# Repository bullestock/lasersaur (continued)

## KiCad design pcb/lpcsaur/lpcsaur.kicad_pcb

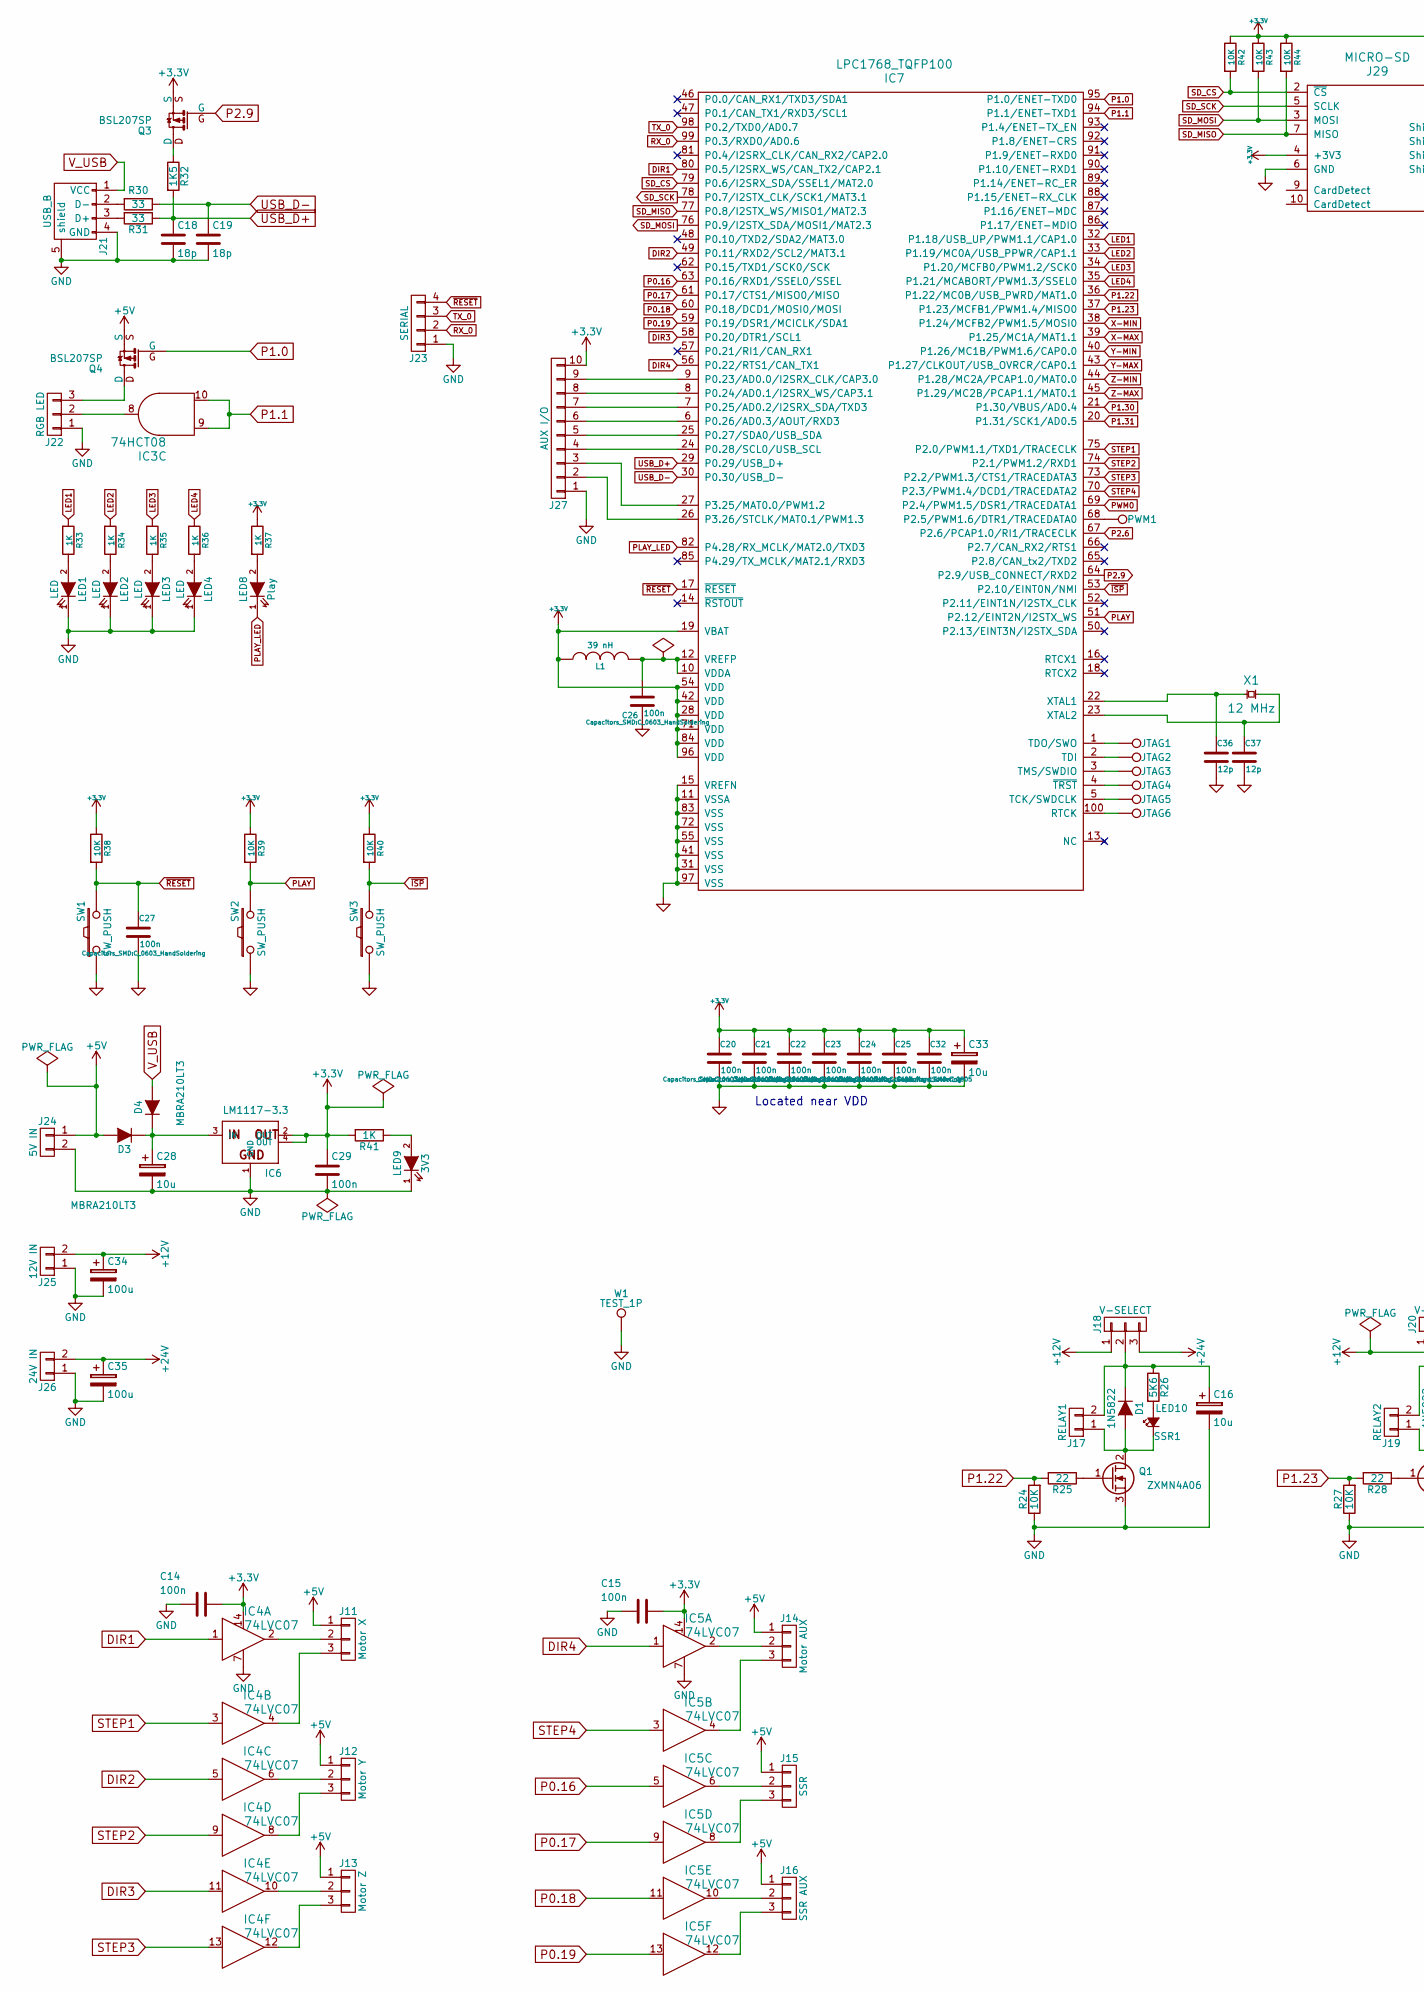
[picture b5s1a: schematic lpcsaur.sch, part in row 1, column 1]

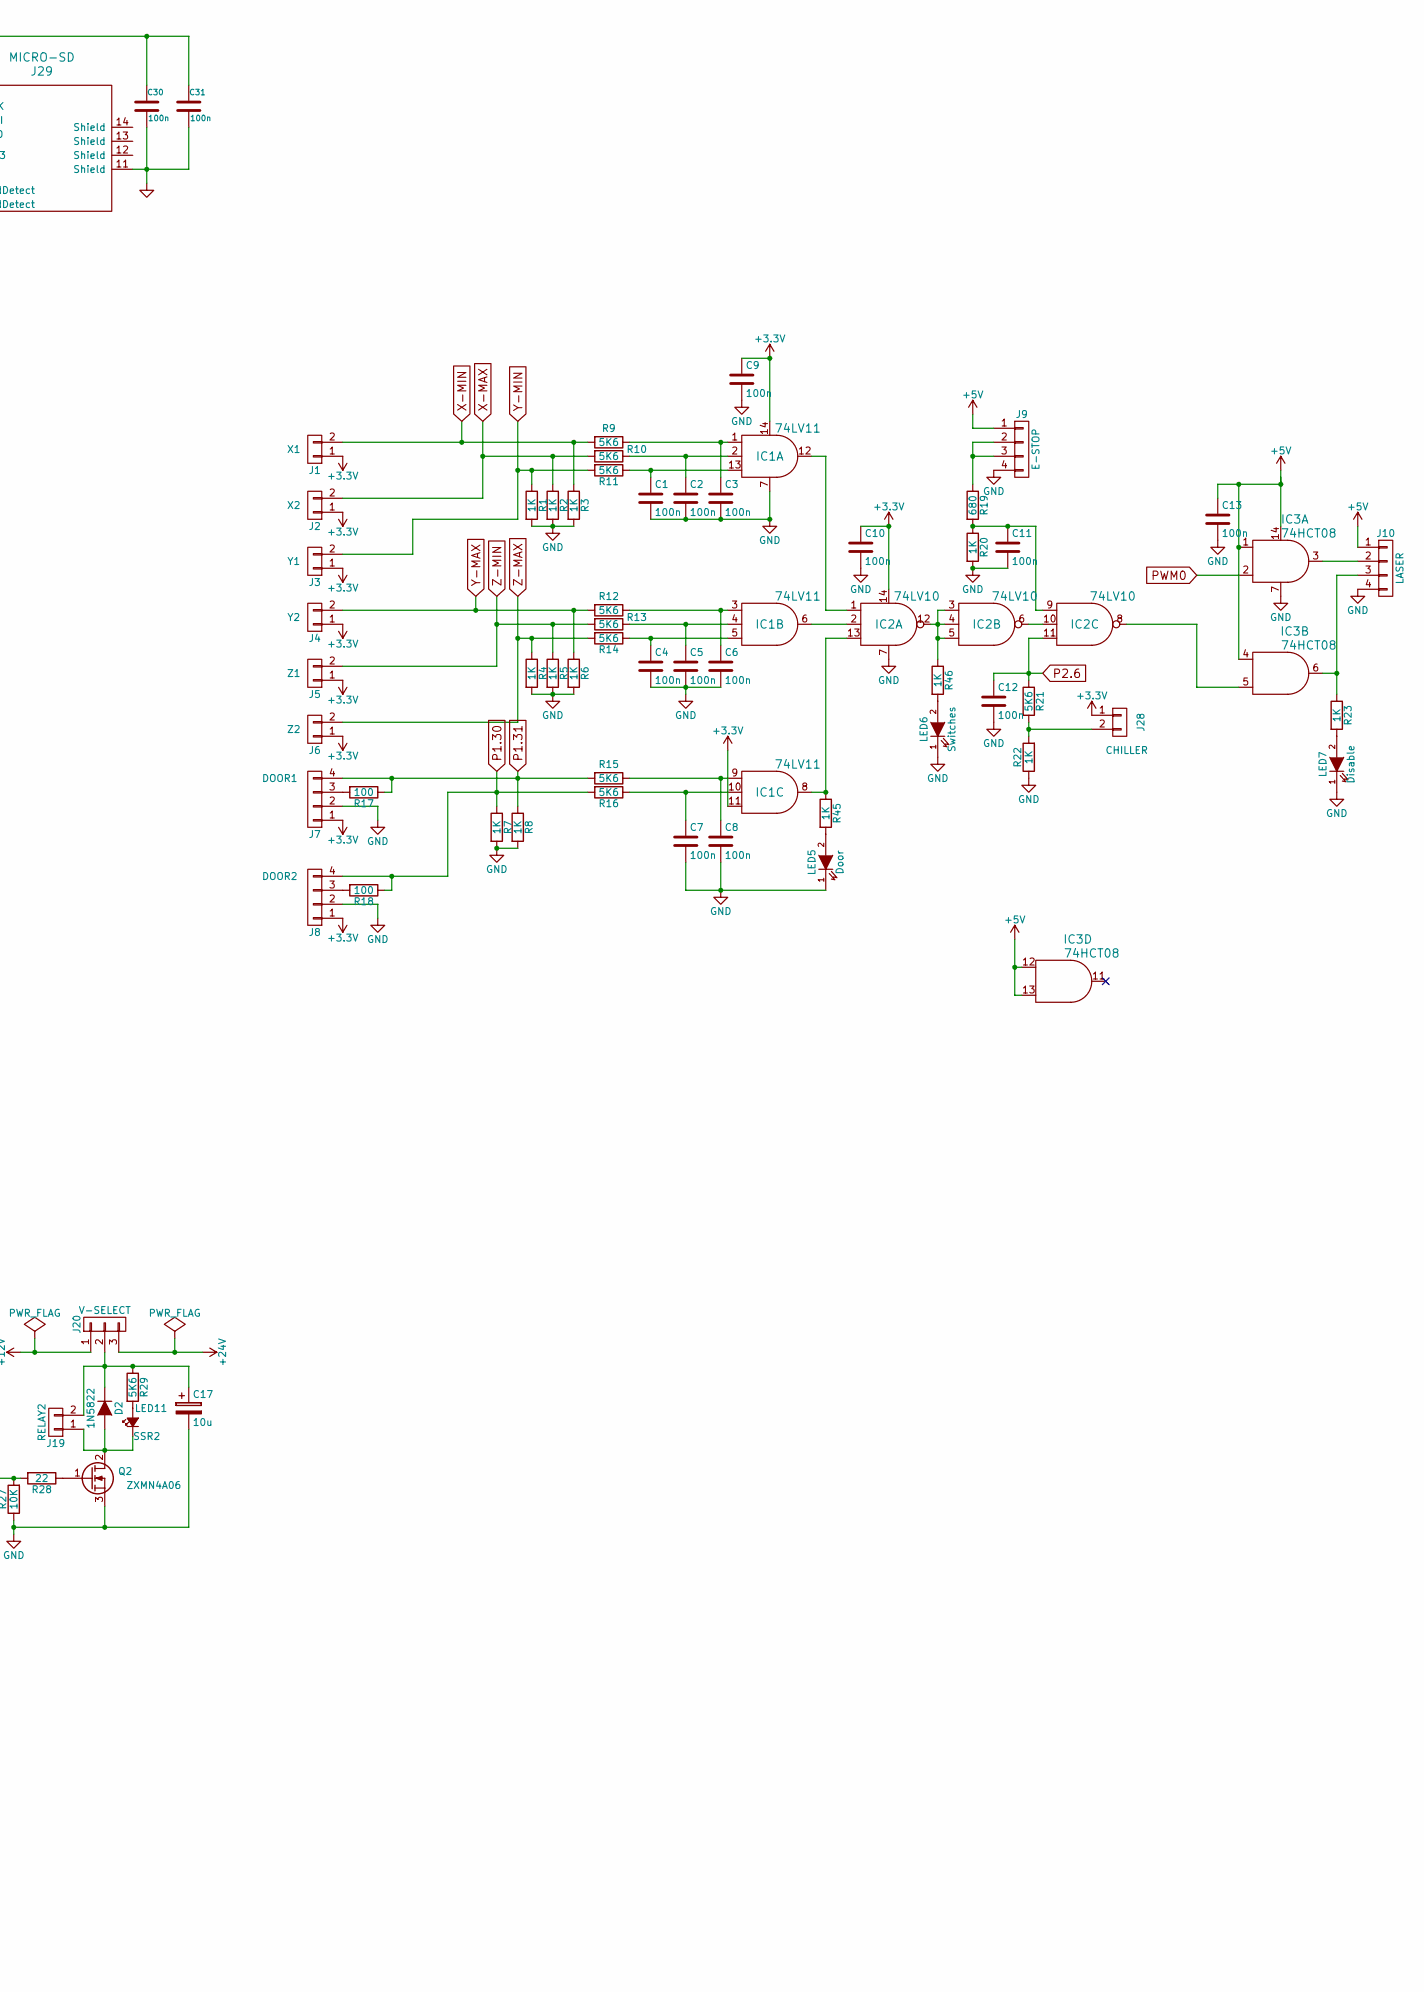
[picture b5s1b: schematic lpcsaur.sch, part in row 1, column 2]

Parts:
C1, C2, C3, C4, C5, C6, C7, C8, C9, C10, C11, C12, C13, C14, C15, C29, C30, C31, C32: 100n; C_0805
C16, C17, C28, C33: 10u; TantalC_SizeD_EIA-7343_Reflow
C18, C19: 18p; C_0603
C20, C21, C22, C23, C24, C25, C26, C27: 100n; C_0603_HandSoldering
C34, C35: 100u; c_elec_6.3x7.7
C36, C37: 12p; C_0603
D1, D2: 1N5822; Diode_DO-41_SOD81_Vertical_KathodeUp
D3, D4: MBRA210LT3; SMA_Standard
IC1: 74LV11; SOIC-14_N
IC2: 74LV10; SSOP-14
IC3: 74HCT08; SOIC-14_N
IC4, IC5: 74LVC07; SOIC-14_N
IC6: LM1117-3.3; SOT-223
IC7: LPC1768_TQFP100; TQFP-100_14x14mm_Pitch0.5mm
J1: X1; JST_PH_B2B-PH-K_02x2.00mm_Straight
J2: X2; JST_PH_B2B-PH-K_02x2.00mm_Straight
J3: Y1; JST_PH_B2B-PH-K_02x2.00mm_Straight
J4: Y2; JST_PH_B2B-PH-K_02x2.00mm_Straight
J5: Z1; JST_PH_B2B-PH-K_02x2.00mm_Straight
J6: Z2; JST_PH_B2B-PH-K_02x2.00mm_Straight
J7: DOOR1; JST_PH_B4B-PH-K_04x2.00mm_Straight
J8: DOOR2; JST_PH_B4B-PH-K_04x2.00mm_Straight
J9: E-STOP; JST_PH_B4B-PH-K_04x2.00mm_Straight
J10: LASER; JST_PH_B4B-PH-K_04x2.00mm_Straight
J11: Motor X; JST_PH_B3B-PH-K_03x2.00mm_Straight
J12: Motor Y; JST_PH_B3B-PH-K_03x2.00mm_Straight
J13: Motor Z; JST_PH_B3B-PH-K_03x2.00mm_Straight
J14: Motor AUX; JST_PH_B3B-PH-K_03x2.00mm_Straight
J15: SSR; JST_PH_B3B-PH-K_03x2.00mm_Straight
J16: SSR AUX; JST_PH_B3B-PH-K_03x2.00mm_Straight
J17: RELAY1; JST_PH_B2B-PH-K_02x2.00mm_Straight
J18, J20: V-SELECT; Socket_Strip_Straight_1x03
J19: RELAY2; JST_PH_B2B-PH-K_02x2.00mm_Straight
J21: USB_B
J22: RGB LED; JST_PH_B3B-PH-K_03x2.00mm_Straight
J23: SERIAL; JST_PH_B4B-PH-K_04x2.00mm_Straight
J24: 5V IN; TerminalBlock_WAGO-804_RM5mm_2pol
J25: 12V IN; TerminalBlock_WAGO-804_RM5mm_2pol
J26: 24V IN; TerminalBlock_WAGO-804_RM5mm_2pol
J27: AUX I/O; JST_PH_B10B-PH-K_10x2.00mm_Straight
J28: CHILLER; JST_PH_B2B-PH-K_02x2.00mm_Straight
J29: MICRO-SD; Conn_uSDcard
JTAG1, JTAG2, JTAG3, JTAG4, JTAG5, JTAG6: TEST_1P; TP_Oblong
L1: 39 nH; R_0603
LED1, LED2, LED3, LED4: LED; LED_0603
LED5: Door; LED_0603
LED6: Switches; LED_0603
LED7: Disable; LED_0603
LED8: Play; LED_0603
LED9: 3V3; LED_0603
LED10: SSR1; LED_0603
LED11: SSR2; LED_0603
PWM1: TEST_1P; TP_Oblong
Q1, Q2: ZXMN4A06; SOT-223-3
Q3, Q4: BSL207SP; SSOP-6-3
R1, R2, R3, R4, R5, R6, R7, R8, R20, R22, R23, R33, R34, R35, R36, R37, R41, R45, R46: 1K; R_0603
R9, R10, R11, R12, R13, R14, R15, R16, R21, R26, R29: 5K6; R_0603
R17, R18: 100; R_0603
R19: 680; R_0603
R24, R27, R38, R39, R40, R42, R43, R44: 10K; R_0603
R25, R28: 22; R_0603
R30, R31: 33; R_0603
R32: 1K5; R_0603
SW1, SW3: SW_PUSH; TactileSwitch
SW2: SW_PUSH; TactileSwitchUpright
W1: TEST_1P; TP_0805
X1: 12 MHz; CrystalSmd2.5x3.2

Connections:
+3V3: C9.1, C10.1, C14.1, C15.1, C20.1, C21.1, C22.1, C23.1, C24.1, C25.1, C29.1, C30.1, C31.1, C32.1, C33.1, IC1.11 (3C), IC1.14 (VDD), IC2.14 (VDD), IC4.14 (VDD), IC5.14 (VDD), IC6.2 (OUT), IC6.4 (OUT), IC7.19 (VBAT), IC7.28 (VDD), IC7.42 (VDD), IC7.54 (VDD), IC7.71 (VDD), IC7.84 (VDD), IC7.96 (VDD), J1.1, J2.1, J3.1, J4.1, J5.1, J6.1, J7.1, J8.1, J27.10, J28.1, J29.4 (+3V3), L1.1, Q3.S, R37.1, R38.1, R39.1, R40.1, R41.2, R42.1, R43.1, R44.1
+5V: C13.1, D3.2 (A), IC3.1 (1A), IC3.4 (2A), IC3.12 (4A), IC3.13 (4B), IC3.14 (VDD), J9.1, J10.1, J11.1, J12.1, J13.1, J14.1, J15.1, J16.1, J24.1, Q4.S
+12V: C34.1, J18.1, J20.1, J25.2
+24V: C35.1, J18.3, J20.3, J26.2
DIR1: IC4.1 (1A), IC7.80 (P0.5/I2SRX_WS/CAN_TX2/CAP2.1)
DIR2: IC4.5 (3A), IC7.49 (P0.11/RXD2/SCL2/MAT3.1)
DIR3: IC4.11 (5A), IC7.58 (P0.20/DTR1/SCL1)
DIR4: IC5.1 (1A), IC7.56 (P0.22/RTS1/CAN_TX1)
GND: C1.2, C2.2, C3.2, C4.2, C5.2, C6.2, C7.2, C8.2, C9.2, C10.2, C11.2, C12.2, C13.2, C14.2, C15.2, C16.2, C17.2, C18.2, C19.2, C20.2, C21.2, C22.2, C23.2, C24.2, C25.2, C26.2, C27.2, C28.2, C29.2, C30.2, C31.2, C32.2, C33.2, C34.2, C35.2, C36.2, C37.2, IC1.7 (VSS), IC2.7 (VSS), IC3.7 (VSS), IC4.7 (VSS), IC5.7 (VSS), IC6.1 (GND), IC7.11 (VSSA), IC7.15 (VREFN), IC7.31 (VSS), IC7.41 (VSS), IC7.55 (VSS), IC7.72 (VSS), IC7.83 (VSS), IC7.97 (VSS), J7.2, J8.2, J9.4, J10.4, J21.4 (GND), J21.5 (shield), J22.1, J23.1, J24.2, J25.1, J26.1, J27.1, J29.6 (GND), J29.9 (CardDetect), J29.11 (Shield), LED1.1 (K), LED2.1 (K), LED3.1 (K), LED4.1 (K), LED5.1 (K), LED6.1 (K), LED7.1 (K), LED9.1 (K), Q1.3 (S), Q2.3 (S), R1.2, R2.2, R3.2, R4.2, R5.2, R6.2, R7.2, R8.2, R20.2, R22.1, R24.1, R27.1, SW1.1, SW2.1, SW3.1, W1.1
LED1: IC7.32 (P1.18/USB_UP/PWM1.1/CAP1.0), R33.2
LED2: IC7.33 (P1.19/MC0A/USB_PPWR/CAP1.1), R34.2
LED3: IC7.34 (P1.20/MCFB0/PWM1.2/SCK0), R35.2
LED4: IC7.35 (P1.21/MCABORT/PWM1.3/SSEL0), R36.2
unnamed: C1.1, IC1.13 (1C), R11.1
unnamed: C2.1, IC1.2 (1B), R10.1
unnamed: C3.1, IC1.1 (1A), R9.1
unnamed: C4.1, IC1.5 (2C), R14.1
unnamed: C5.1, IC1.4 (2B), R13.1
unnamed: C6.1, IC1.3 (2A), R12.1
unnamed: C7.1, IC1.10 (3B), R16.1
unnamed: C8.1, IC1.9 (3A), R15.1
unnamed: C11.1, IC2.9 (3A), R19.2, R20.1
unnamed: C16.1, D1.1 (K), J17.2, J18.2, R26.1
unnamed: C17.1, D2.1 (K), J19.2, J20.2, R29.1
unnamed: C26.1, IC7.10 (VDDA), IC7.12 (VREFP), L1.2
unnamed: C28.1, D3.1 (K), D4.1 (K), IC6.3 (IN)
unnamed: C36.1, IC7.22 (XTAL1), X1.1
unnamed: C37.1, IC7.23 (XTAL2), X1.2
unnamed: D1.2 (A), J17.1, LED10.1 (K), Q1.2 (D)
unnamed: D2.2 (A), J19.1, LED11.1 (K), Q2.2 (D)
unnamed: IC1.6 (2Y), IC2.2 (1B)
unnamed: IC1.8 (3Y), IC2.13 (1C), R45.1
unnamed: IC1.12 (1Y), IC2.1 (1A)
unnamed: IC2.8 (3Y), IC3.5 (2B)
unnamed: IC2.6 (2Y), IC2.10 (3B)
unnamed: IC2.3 (2A), IC2.4 (2B), IC2.5 (2C), IC2.12 (1Y), R46.1
unnamed: IC3.3 (1Y), J10.2
unnamed: IC3.6 (2Y), J10.3, R23.1
unnamed: IC3.8 (3Y), J22.2
unnamed: IC4.2 (1Y), J11.2
unnamed: IC4.4 (1Y), J11.3
unnamed: IC4.6 (1Y), J12.2
unnamed: IC4.8 (1Y), J12.3
unnamed: IC4.10 (1Y), J13.2
unnamed: IC4.12 (1Y), J13.3
unnamed: IC5.2 (1Y), J14.2
unnamed: IC5.4 (1Y), J14.3
unnamed: IC5.6 (1Y), J15.2
unnamed: IC5.8 (1Y), J15.3
unnamed: IC5.10 (1Y), J16.2
unnamed: IC5.12 (1Y), J16.3
unnamed: IC7.1 (TDO/SWO), JTAG1.1
unnamed: IC7.2 (TDI), JTAG2.1
unnamed: IC7.3 (TMS/SWDIO), JTAG3.1
unnamed: IC7.4 (~TRST), JTAG4.1
unnamed: IC7.5 (TCK/SWDCLK), JTAG5.1
unnamed: IC7.6 (P0.26/AD0.3/AOUT/RXD3), J27.6
unnamed: IC7.7 (P0.25/AD0.2/I2SRX_SDA/TXD3), J27.7
unnamed: IC7.8 (P0.24/AD0.1/I2SRX_WS/CAP3.1), J27.8
unnamed: IC7.9 (P0.23/AD0.0/I2SRX_CLK/CAP3.0), J27.9
unnamed: IC7.24 (P0.28/SCL0/USB_SCL), J27.4
unnamed: IC7.25 (P0.27/SDA0/USB_SDA), J27.5
unnamed: IC7.26 (P3.26/STCLK/MAT0.1/PWM1.3), J27.2
unnamed: IC7.27 (P3.25/MAT0.0/PWM1.2), J27.3
unnamed: IC7.68 (P2.5/PWM1.6/DTR1/TRACEDATA0), PWM1.1
unnamed: IC7.100 (RTCK), JTAG6.1
unnamed: J7.3, R17.2
unnamed: J8.3, R18.2
unnamed: J9.2, J9.3, R19.1
unnamed: J21.2 (D-), R30.2
unnamed: J21.3 (D+), R31.2
unnamed: J22.3, Q4.D
unnamed: J28.2, R21.2, R22.2
unnamed: LED1.2 (A), R33.1
unnamed: LED2.2 (A), R34.1
unnamed: LED3.2 (A), R35.1
unnamed: LED4.2 (A), R36.1
unnamed: LED5.2 (A), R45.2
unnamed: LED6.2 (A), R46.2
unnamed: LED7.2 (A), R23.2
unnamed: LED8.2 (A), R37.2
unnamed: LED9.2 (A), R41.1
unnamed: LED10.2 (A), R26.2
unnamed: LED11.2 (A), R29.2
unnamed: Q1.1 (G), R25.1
unnamed: Q2.1 (G), R28.1
unnamed: Q3.D, R32.1
P0.16: IC5.5 (3A), IC7.63 (P0.16/RXD1/SSEL0/SSEL)
P0.17: IC5.9 (4A), IC7.61 (P0.17/CTS1/MISO0/MISO)
P0.18: IC5.11 (5A), IC7.60 (P0.18/DCD1/MOSI0/MOSI)
P0.19: IC5.13 (6A), IC7.59 (P0.19/DSR1/MCICLK/SDA1)
P1.0: IC7.95 (P1.0/ENET-TXD0), Q4.G
P1.1: IC3.9 (3A), IC3.10 (3B), IC7.94 (P1.1/ENET-TXD1)
P1.22: IC7.36 (P1.22/MC0B/USB_PWRD/MAT1.0), R24.2, R25.2
P1.23: IC7.37 (P1.23/MCFB1/PWM1.4/MISO0), R27.2, R28.2
P1.30: IC7.21 (P1.30/VBUS/AD0.4), J8.4, R7.1, R16.2, R18.1
P1.31: IC7.20 (P1.31/SCK1/AD0.5), J7.4, R8.1, R15.2, R17.1
P2.6: C12.1, IC2.11 (3C), IC7.67 (P2.6/PCAP1.0/RI1/TRACECLK), R21.1
P2.9: IC7.64 (P2.9/USB_CONNECT/RXD2), Q3.G
PLAY: IC7.51 (P2.12/EINT2N/I2STX_WS), R39.2, SW2.2
PLAY_LED: IC7.82 (P4.28/RX_MCLK/MAT2.0/TXD3), LED8.1 (K)
PWM0: IC3.2 (1B), IC7.69 (P2.4/PWM1.5/DSR1/TRACEDATA1)
RX_0: IC7.99 (P0.3/RXD0/AD0.6), J23.2
SD_CS: IC7.79 (P0.6/I2SRX_SDA/SSEL1/MAT2.0), J29.2 (~CS), R42.2
SD_MISO: IC7.77 (P0.8/I2STX_WS/MISO1/MAT2.3), J29.7 (MISO), R44.2
SD_MOSI: IC7.76 (P0.9/I2STX_SDA/MOSI1/MAT2.3), J29.3 (MOSI), R43.2
SD_SCK: IC7.78 (P0.7/I2STX_CLK/SCK1/MAT3.1), J29.5 (SCLK)
STEP1: IC4.3 (2A), IC7.75 (P2.0/PWM1.1/TXD1/TRACECLK)
STEP2: IC4.9 (4A), IC7.74 (P2.1/PWM1.2/RXD1)
STEP3: IC4.13 (6A), IC7.73 (P2.2/PWM1.3/CTS1/TRACEDATA3)
STEP4: IC5.3 (2A), IC7.70 (P2.3/PWM1.4/DCD1/TRACEDATA2)
TX_0: IC7.98 (P0.2/TXD0/AD0.7), J23.3
USB_D+: C18.1, IC7.29 (P0.29/USB_D+), R31.1, R32.2
USB_D-: C19.1, IC7.30 (P0.30/USB_D-), R30.1
V_USB: D4.2 (A), J21.1 (VCC)
X-MAX: IC7.39 (P1.25/MC1A/MAT1.1), J2.2, R2.1, R10.2
X-MIN: IC7.38 (P1.24/MCFB2/PWM1.5/MOSI0), J1.2, R3.1, R9.2
Y-MAX: IC7.43 (P1.27/CLKOUT/USB_OVRCR/CAP0.1), J4.2, R6.1, R12.2
Y-MIN: IC7.40 (P1.26/MC1B/PWM1.6/CAP0.0), J3.2, R1.1, R11.2
Z-MAX: IC7.45 (P1.29/MC2B/PCAP1.1/MAT0.1), J6.2, R4.1, R14.2
Z-MIN: IC7.44 (P1.28/MC2A/PCAP1.0/MAT0.0), J5.2, R5.1, R13.2
~ISP: IC7.53 (P2.10/EINT0N/NMI), R40.2, SW3.2
~RESET: C27.1, IC7.17 (~RESET), J23.4, R38.2, SW1.2

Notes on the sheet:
Located near VDD

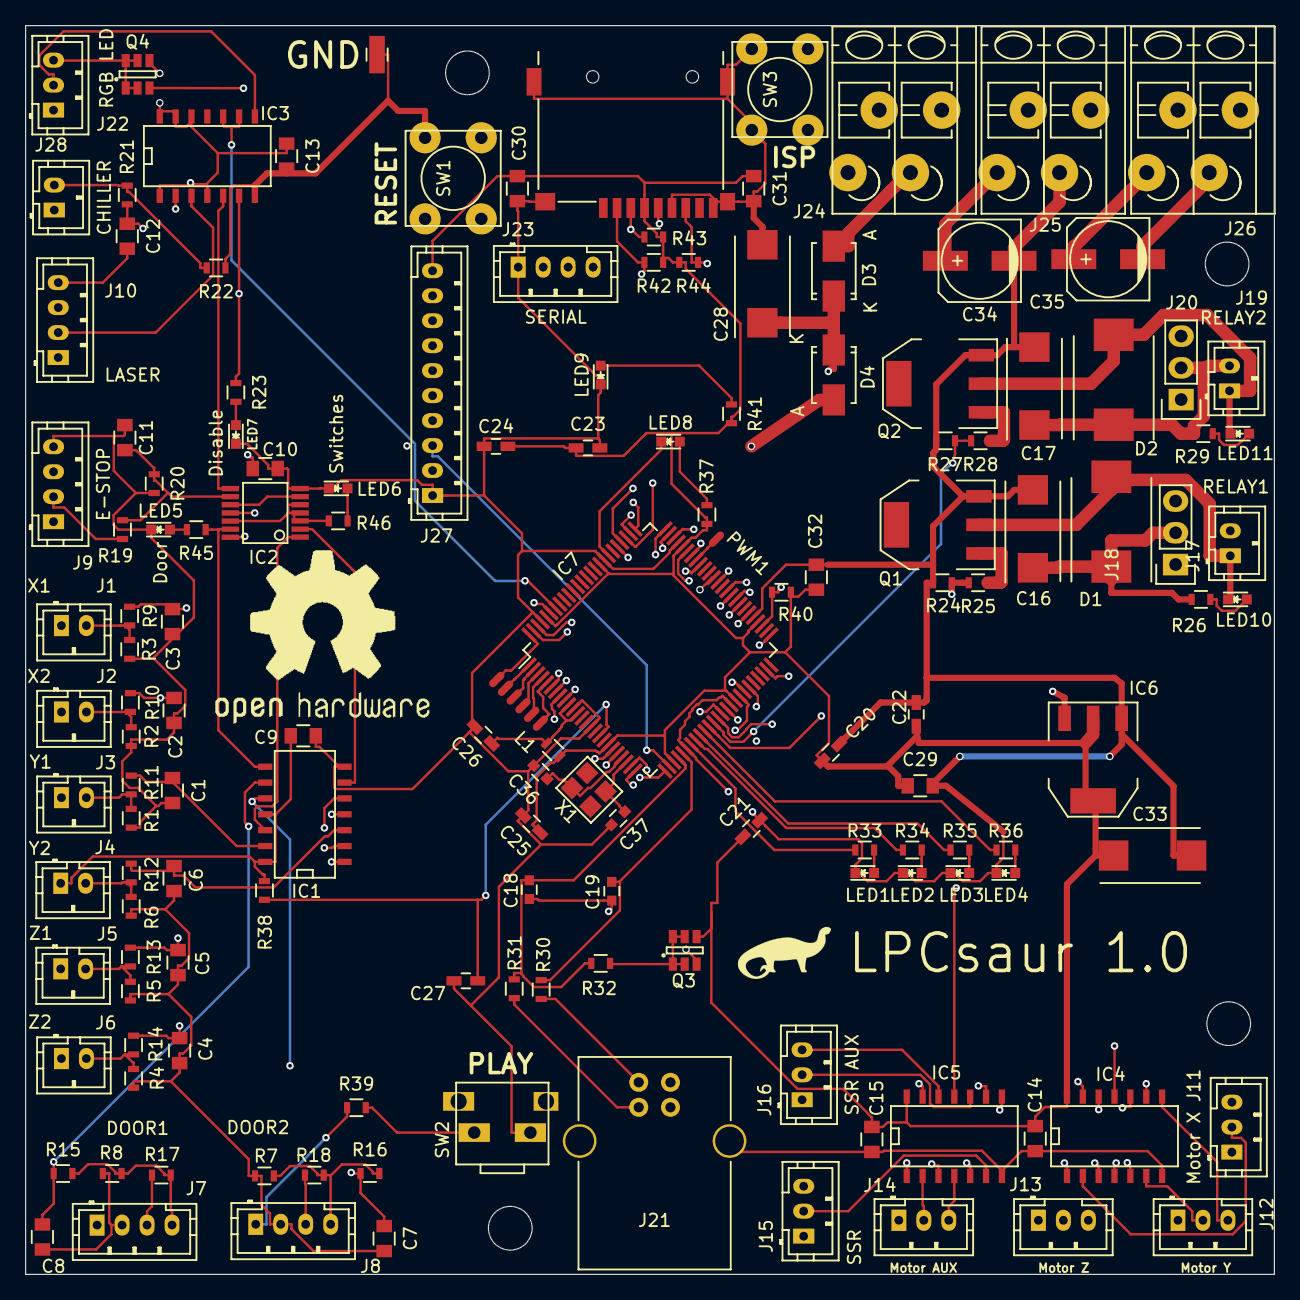
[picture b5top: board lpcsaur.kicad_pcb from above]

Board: 4 copper layers, 100.0 x 100.0 mm, 157 parts (0 on the bottom side), 123 nets.

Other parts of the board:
G1: LOGO; dino
G2: LOGO; OSHWLOGO0.75IN
HOLE1, HOLE2, HOLE3, HOLE4: MountingHole_3.5mm

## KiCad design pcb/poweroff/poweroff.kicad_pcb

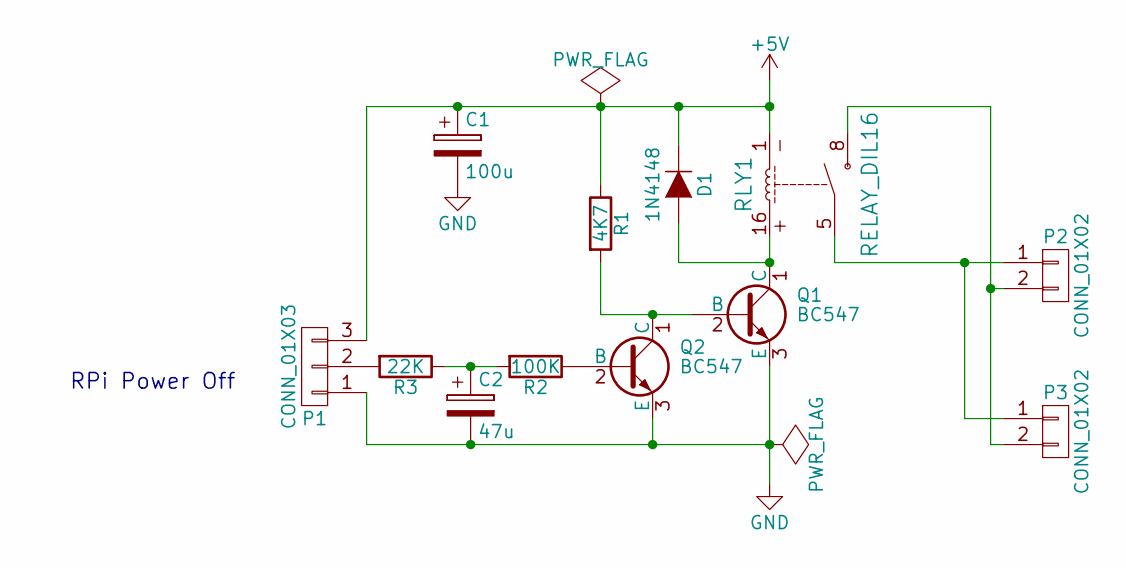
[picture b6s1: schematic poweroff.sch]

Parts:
C1: 100u; C_Disc_D6_P5
C2: 47u; C_Disc_D6_P5
D1: 1N4148; Diode_DO-41_SOD81_Horizontal_RM10
P1: CONN_01X03; JST_PH_B3B-PH-K_03x2.00mm_Straight
P2, P3: CONN_01X02; TerminalBlock_WAGO-804_RM5mm_2pol
Q1, Q2: BC547; TO-92_Molded_Narrow_CBE
R1: 4K7; Resistor_Horizontal_RM10mm
R2: 100K; Resistor_Horizontal_RM10mm
R3: 22K; Resistor_Horizontal_RM10mm
RLY1: RELAY_DIL16; DIP-16_Relay

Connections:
+5V: C1.1, D1.1 (K), P1.3, R1.1, RLY1.1
GND: C1.2, C2.2, P1.1, Q1.3 (E), Q2.3 (E)
unnamed: C2.1, R2.2, R3.1
unnamed: D1.2 (A), Q1.1 (C), RLY1.16
unnamed: P1.2, R3.2
unnamed: P2.1, P3.1, RLY1.5
unnamed: P2.2, P3.2, RLY1.8
unnamed: Q1.2 (B), Q2.1 (C), R1.2
unnamed: Q2.2 (B), R2.1

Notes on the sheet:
RPi Power Off

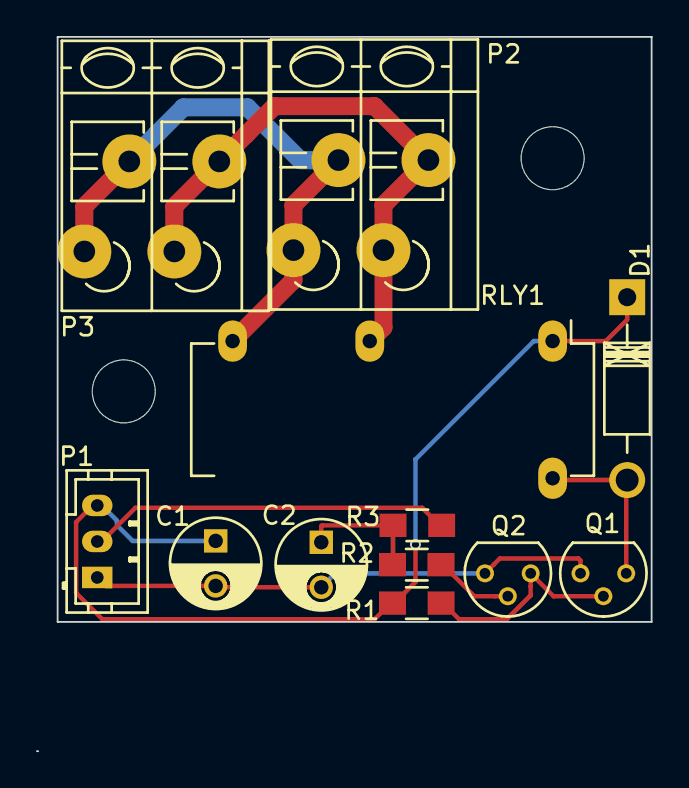
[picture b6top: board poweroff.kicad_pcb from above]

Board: 2 copper layers, 33.0 x 32.5 mm, 14 parts (0 on the bottom side), 9 nets.

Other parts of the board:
H1, H2: MountingHole_3.5mm

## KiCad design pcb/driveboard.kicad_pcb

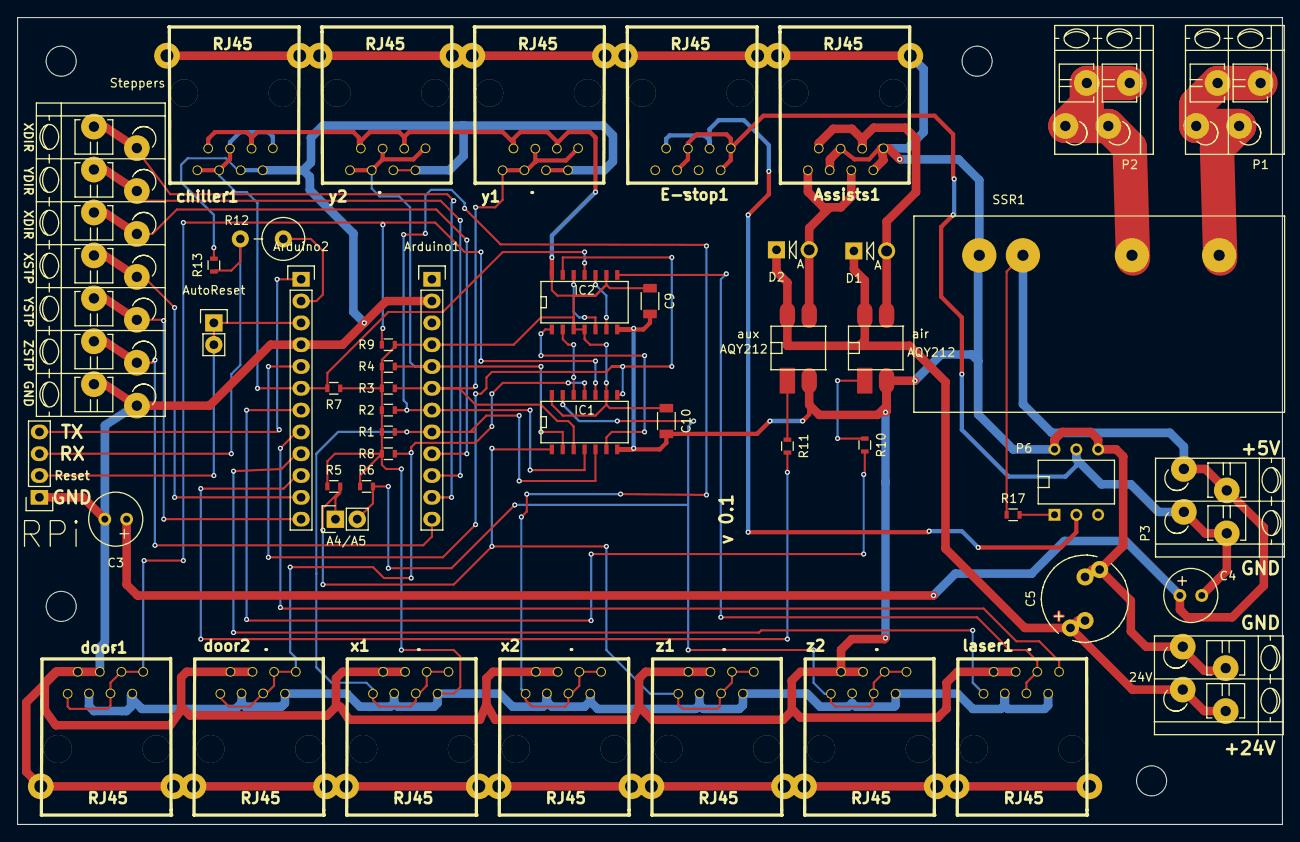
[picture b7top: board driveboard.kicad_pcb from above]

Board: 2 copper layers, 147.3 x 94.0 mm, 50 parts (0 on the bottom side), 42 nets.

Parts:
24V: CONN_01X02; TerminalBlock_WAGO-804_RM5mm_2pol
A4/A5: Header; Pin_Header_Straight_1x02
Arduino1, Arduino2: Header; Pin_Header_Straight_1x12
Assists1: RJ45; RJ45-8-shield
AutoReset: CONN_01X02; Pin_Header_Straight_1x02
C3: 10u; Elko_vert_11.2x6.3mm_RM2.5
C4: 47u; Elko_vert_11.2x6.3mm_RM2.5
C5: 1000u; Elko_vert_20x10mm_RM5to7.5
C9, C10: 100n; C_1206
D1, D2: 1N4004; Diode_DO-41_SOD81_Vertical_AnodeUp
E-stop1: RJ45; RJ45-8-shield
IC1: 7411; SOIC-14_N
IC2: 7410; SOIC-14_N
MH: MountingHole_3-5mm
P1: AC IN; TerminalBlock_WAGO-804_RM5mm_2pol
P2: AC out; TerminalBlock_WAGO-804_RM5mm_2pol
P3: 5V in; TerminalBlock_WAGO-804_RM5mm_2pol
P6: AQV2526; DIP-6__300
R1, R2, R3, R4, R5, R6, R7, R8, R9, R13: 10K; R_0603
R10, R11, R17: 360R; R_0603
R12: 6K5; Resistor_Vertical_RM5mm
RPi: CONN_01X04; Pin_Header_Straight_1x04
SSR1: PF240D25; CrydomPF240
Steppers: Screw terminal; TerminalBlock_WAGO-804_RM5mm_7pol
air: AQY212; DIP-4_SMD_300
aux: AQY212; DIP-4_SMD_300
chiller1: RJ45; RJ45-8-shield
door1, door2: RJ45; RJ45-8-shield
laser1: RJ45; RJ45-8-shield
x1, x2: RJ45; RJ45-8-shield
y1, y2: RJ45; RJ45-8-shield
z1, z2: RJ45; RJ45-8-shield

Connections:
GND: 24V.2, Arduino1.2, Arduino2.4, Assists1.2, Assists1.4, Assists1.6, Assists1.8, Assists1.9, C3.2, C5.2, C9.2, C10.2, E-stop1.9, IC1.7, IC2.7, P6.4, P6.6, R13.2, RPi.1, SSR1.4, Steppers.7, air.2, aux.2, chiller1.7, chiller1.8, chiller1.9, door1.7, door1.8, door1.9, door2.7, door2.8, door2.9, laser1.7, laser1.8, laser1.9, x1.7, x1.8, x1.9, x2.7, x2.8, x2.9, y1.7, y1.8, y1.9, y2.7, y2.8, y2.9, z1.7, z1.8, z1.9, z2.7, z2.8, z2.9
unnamed: 24V.1, C5.1, D1.1, D2.1, air.4, aux.4
unnamed: A4/A5.1, IC1.1, R5.2, z1.2, z1.4, z1.5, z1.6
unnamed: A4/A5.2, IC1.13, R6.2, z2.2, z2.4, z2.5, z2.6
unnamed: Arduino1.4, C9.1, C10.1, IC1.9, IC1.14, IC2.3, IC2.4, IC2.9, IC2.14, R1.1, R2.1, R3.1, R4.2, R5.1, R6.1, R7.1, R8.1, R9.1, chiller1.1, chiller1.3, door1.1, door1.3, door2.1, door2.3, laser1.1, laser1.3, x1.1, x1.3, x2.1, x2.3, y1.1, y1.3, y2.1, y2.3, z1.1, z1.3, z2.1, z2.3
unnamed: Arduino1.5, IC1.2, R4.1, y2.2, y2.4, y2.5, y2.6
unnamed: Arduino1.6, IC1.3, R3.2, y1.2, y1.4, y1.5, y1.6
unnamed: Arduino1.7, IC1.4, R2.2, x2.2, x2.4, x2.5, x2.6
unnamed: Arduino1.8, IC1.5, R1.2, x1.2, x1.4, x1.5, x1.6
unnamed: Arduino1.9, Steppers.3
unnamed: Arduino1.10, Steppers.2
unnamed: Arduino1.11, Steppers.1
unnamed: Arduino1.12, Steppers.6
unnamed: Arduino2.1, RPi.4
unnamed: Arduino2.2, R12.1, RPi.3
unnamed: Arduino2.3, AutoReset.1, AutoReset.2, RPi.2
unnamed: Arduino2.5, IC1.8, IC2.13
unnamed: Arduino2.6, IC2.11, R7.2, chiller1.2, chiller1.4, chiller1.5, chiller1.6
unnamed: Arduino2.7, R10.2
unnamed: Arduino2.8, laser1.5
unnamed: Arduino2.9, laser1.4
unnamed: Arduino2.10, R11.2
unnamed: Arduino2.11, Steppers.4
unnamed: Arduino2.12, Steppers.5
unnamed: Assists1.1, Assists1.3, D1.2, air.3
unnamed: Assists1.5, Assists1.7, D2.2, aux.3
unnamed: C3.1, C4.1, P3.2, R17.1, SSR1.3
unnamed: C4.2, E-stop1.2, E-stop1.4, E-stop1.6, E-stop1.8, P3.1, P6.5
unnamed: E-stop1.1, E-stop1.3, P6.2
unnamed: IC1.6, IC2.1
unnamed: IC1.10, R9.2, door1.2, door1.4, door1.5, door1.6
unnamed: IC1.11, R8.2, door2.2, door2.4, door2.5, door2.6
unnamed: IC1.12, IC2.2
unnamed: IC2.8, laser1.2, laser1.6
unnamed: IC2.6, IC2.10
unnamed: IC2.5, IC2.12
unnamed: P1.1, P1.2, SSR1.1
unnamed: P2.1, P2.2, SSR1.2
unnamed: P6.1, R17.2
unnamed: R10.1, air.1
unnamed: R11.1, aux.1
unnamed: R12.2, R13.1

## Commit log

2015-06-09 Add first complete version.
2015-07-23 Bugfix: Change R1-R9 from pullups to pulldowns.
2015-07-23 Use Protel filename extensions for the sake of dirtypcbs.com.
2015-07-23 Update.
2015-07-23 Use Protel extensions.
2015-07-24 Re-add Vcc connection.
2015-08-20 Fix wrong label.
2016-04-07 Initial HW test.
2016-04-12 Fix bugs in demo program.
2016-04-12 Seems to work.
2016-05-06 Show orange if DIS is high and PWM is active.
2016-05-06 Add relaybox V2 schematic.
2016-05-21 Rename Arduino sketch. Update diagram.
2016-05-22 Use 3 LEDs.
2016-05-28 DriveBoard, now with more oomph.
2016-06-10 Starting on new Smoothieware-compatible driveboard.
2016-06-10 All components placed.
2016-06-11 Annotate.
2016-06-11 Make ERC pass.
2016-06-16 Diagram done, routing in progress.
2016-06-18 Fix 7410 footprint.
2016-06-19 Complete routing.
2016-06-19 Add ground/power fill. Fix labels.
2016-06-21 10 x 10 cm layout.
2016-06-25 Increase width of power tracks. Clean up silk screen.
2016-06-27 Reduce size.
2016-06-27 Rename 10x10 to lpcsaur; delete original lpcsaur folder.
2016-07-17 Fix footprint for Q3, Q4.
2016-08-14 Fix minor silkscreen issues.
2016-11-26 Add.
2016-12-11 First shot.
2016-12-13 Fix sign extension bug.
2016-12-17 Add part 2.
2016-12-17 Introduction.
2016-12-18 Remove recess.
2016-12-18 Remove recess, and make rod/screwholes have bottoms.
2016-12-27 Update stencil notes.
2016-12-27 Add kinematic base.
2016-12-29 Fix nut hole bug.
2016-12-29 Add support.
2017-02-11 Enlarge X axis to increase clearance for adjustment screw.
2017-04-16 Add interlock board for MKS SBASE.
2017-04-22 More work on PCB.
2017-04-22 Finish routing.
2017-04-22 Adjust labels.
2017-04-29 Fix bug where door inputs were connected before the filter.
2017-04-30 Mount plates.
2017-05-01 Change D1 to SS34.
2017-05-01 Fix placement of logo on back.
2017-05-06 Add RPi.
2017-06-01 Fix ethernet jack.
2017-06-08 Fix water holes.
2017-07-12 Config file for Smoothieware.
2017-07-12 Final version.
2017-07-29 Disable pull-up on door switches; add chiller switch block.
2017-07-29 Add more pictures.
2017-07-29 Add OHW logos.
2017-07-29 For now, just set 'limits OK' high always.
2017-07-29 Fix door switch high/low.
2017-07-30 Use 115200 baud.
2018-12-08 Exhaust is controlled by HEATER2.
2019-01-26 Rename, and update to KiCad V5.
2019-01-26 Remove rescure symbols.
2019-01-26 Fix footprints.
2019-02-27 Add chiller control.
2019-03-17 Integrate chiller control.
2019-03-17 Fix wrong supply voltage to IC1.
2019-05-03 Add inverted laser control signal.
2019-05-06 Fix overlapping silk screen.
2019-06-20 Old settings.
2019-06-20 Fix current settings.
2019-11-21 First version.
2019-12-07 No longer used.
2019-12-07 ITX + 3.5" disk
2019-12-07 MKS-SBASE + aux logic board
2019-12-07 DC-DC converter for ITX power
2019-12-07 Final fixes.
2019-12-07 Run SSR off 24 V.
2019-12-20 Update for vertical mounting.
2019-12-20 For MKS-SBASE and aux board.
2019-12-22 First attempt.
2019-12-22 Make hole part of flange.
2019-12-22 Control board for usage counter.
2019-12-26 Make right-handed version.
2019-12-26 Revert.
2019-12-26 Make mirrored version.
2019-12-30 Use correct signal.
2020-01-01 Fix track widths, outline.
2020-01-04 Add new stuff.
2020-01-19 Fix error.
2020-02-10 First trial.
2020-02-15 Add outer part.
2020-02-15 Enlarge insert hole.
2020-02-15 Flip, and put feet on.
2020-02-16 Reduce insert hole size.
2020-02-22 Make it thicker.
2020-02-22 Fix holes.
2020-04-08 Remove ridges.
2020-04-08 Get rid of magic numbers.
2020-04-08 Reduce repetition.
2020-04-08 Get rid of magic number.
2020-04-08 Adapt for flat vertical spring.
2020-07-12 Add ridges for X spring.
2020-07-12 Make room for Y bump.
2020-07-13 Add bump for Y spring.
2020-07-15 Adjust dimensions.
2021-06-26 Update to KiCad 5 format; add relay.
2021-07-03 Mess around.
2021-07-03 Split into two parts.
2021-07-04 Fix upper mounting hole positions; enlarge large holes slightly.
2021-07-16 Update for Arch.
2021-07-16 Check checksum.
2021-07-22 Simple app for reading pressure sensor via I2C.
